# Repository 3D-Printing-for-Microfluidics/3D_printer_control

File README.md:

# 3D Printer Control System

A sophisticated control system for custom DLP-SLA 3D printers, built with Flask and WebSocket communication. This system provides a robust web interface for controlling and monitoring 3D printing operations, with support for various hardware configurations and real-time feedback.

# Overview

This system is designed to control custom DLP-SLA 3D printers using a JSON-based print file format. The print files are validated using a custom JSON schema validator to ensure proper formatting and compatibility. The system supports multiple printer configurations and can be adapted to different hardware setups through its modular architecture.

## System Architecture

### Backend
- Built on Flask web server with modular blueprint structure
- Uses Socket.IO for real-time bidirectional communication between frontend and backend
- Implements a modular hardware driver system for various printer components
- Database-driven job queue management using SQLAlchemy
- Comprehensive logging system with configurable levels and file rotation
- Error handling and recovery mechanisms for hardware failures

### Frontend
- JINJA2 templating engine for HTML structure
- Bootstrap (Darkly theme) for responsive styling
- JavaScript libraries:
  - Socket.IO for real-time communication
  - AJAX for asynchronous requests
  - jQuery for DOM manipulation
  - Popper.js for tooltips and popovers
- Dynamic UI updates for real-time printer status
- Responsive design for various screen sizes

## Hardware Configuration

The system uses a flexible hardware configuration system that:
- Loads hardware configurations based on device hostname
- Supports multiple types of hardware drivers:
  - Virtual hardware (screen, coord_systems, external_control)
  - Abstract base classes and generic drivers (e.g., Visitech light engine, ACS XY/BP stage, Hexapod TTR/focus stage)
  - Regular hardware drivers
- Includes firmware management capabilities through `flash_firmware.sh` RPi script
- Provides dummy drivers for testing and development
- Supports hardware-specific calibration and configuration
- Implements hardware abstraction layers for consistent control interfaces

### Hardware Types
1. **Motion Control**
   - XY stages (ACS, custom implementations)
   - Z-axis control
   - Build plate control
   - Tip-tilt-rotate (TTR) stages
   - Focus stages

2. **Light Control**
   - DLP light engines
   - Screen control systems

3. **Sensors**
   - Load cells
   - Keyence sensors
   - Environmental sensors
   - Accelerometers
   - Light measurement systems

4. **Auxiliary Systems**
   - Vacuum control
   - GPIO control
   - Film control
   - Environmental monitoring

## Core Components

### Manual Controls
- Each hardware driver has associated frontend controls
- Automatically populated based on hardware configuration
- Provides fine-grained control over hardware components
- Allows modification of system settings
- Real-time feedback and status updates
- Safety interlocks and emergency stop functionality

### Views
1. **Print History**
   - Displays recent prints with detailed information
   - Enables job download and re-queue functionality
   - Print success/failure statistics
   - Job parameter history

2. **Server Logs**
   - Shows last 2 weeks of logs
   - Includes calibration position logs
   - Hardware-specific diagnostic information
   - Error tracking and debugging tools

3. **Calibration**
   - Manages printer calibration settings
   - Supports focus, tip, tilt adjustments
   - Integrates with Keyence sensors and Hexapod systems
   - Calibration profile management
   - Automated calibration routines

### Main Printer Control (home.py)
The central control system that:
- Manages print uploads and job queue
- Handles printer planarization
- Controls print operations (start/pause/resume/stop)
- Provides real-time feedback (loadcell data, log messages)
- Implements a dynamic class hierarchy for hardware control
- Error handling and recovery
- State management and synchronization

## Hardware Control Architecture

The system uses a dynamic class composition approach:
- Base `print_control` class defines core functionality
- Hardware-specific subclasses extend functionality
- Class composition is determined by hardware configuration
- Import order is critical for proper initialization and print operations
- Thread-safe operation handling
- Event-driven architecture for hardware interactions

# Raspberry Pi Deployment

This section details the setup process for deploying the system on a Raspberry Pi 5 with NVME storage. See also the `How to do a full install of a HR5 Raspberry Pi` ProjectWiki page for a more detailed guide with rationale.

### Hardware Requirements

- Raspberry Pi 5
- Pimoroni NVME base
- Crucial P3 Plus 1TB SSD (or compatible)
- External SSD housing (for initial setup)

### Initial Setup

1. **Physical Setup**
   - Install NVME SSD and Pimoroni NVME base
   - Follow [Pimoroni NVME base tutorial](https://learn.pimoroni.com/article/getting-started-with-nvme-base)

2. **OS Installation**
   - Download Raspberry Pi Imager
   - Flash Raspberry Pi OS (64-bit) 2024-03-15
   - Configure initial settings:
     - Set hostname (e.g., HR5, MR1v1, HR3v3)
     - Username: pi
     - Password: 3dprinter
     - Timezone: Denver
     - Enable SSH

3. **System Configuration**
   - Configure SSD boot:
     ```bash
     # Edit /boot/firmware/config.txt
     dtparam=pciex1
     nvme_core.default_ps_max_latency_us=0 pcie_aspm=off
     
     # Configure EEPROM
     sudo rpi-eeprom-config --edit
     # Set:
     BOOT_ORDER=0xf416
     PCIE_PROBE=1
     ```
   - Set system clock: `date -s 'YYYY-MM-DD HH:MM:SS'`
   - Configure network:
     - Connect to BYU-Wifi via https://onboard.byu.edu/guest/public/index.html
     - Set static ethernet address (192.168.0.1/24) using `sudo nmtui`
   - Switch to legacy X11:
     ```bash
     sudo raspi-config
     # Advanced Options -> Wayland -> X11
     ```
   - Disable screen blanking:
     ```bash
     sudo raspi-config
     # Display Options -> Screen Blanking -> No
     ```

4. **USB Device Configuration**
   - Create udev rules for USB devices:
     ```bash
     # Wintech
     sudo nano /etc/udev/rules.d/99-wintech.rules
     SUBSYSTEM=="usb",ATTRS{idVendor}=="0451",ATTRS{idProduct}=="c900",GROUP="users",MODE:="0666"
     
     # MKS Controller
     sudo nano /etc/udev/rules.d/99-mks.rules
     SUBSYSTEM=="usb",ATTRS{idVendor}=="0403",ATTRS{idProduct}=="6001",GROUP="users",MODE:="0666"
     
     # Thorlabs Power Meter
     sudo nano /etc/udev/rules.d/99-thorlabspm100.rules
     SUBSYSTEM=="usb",ATTRS{idVendor}=="1313",ATTRS{idProduct}=="8072",GROUP="users",MODE:="0666"
     ```
   - Reload udev rules: `sudo udevadm control --reload-rules`

5. **System Logging**
   - Configure journald:
     ```bash
     # Edit /etc/systemd/journald.conf
     [Journal]
     MaxRetentionSec=1week
     MaxFileSec=1day
     
     # Create journal directory
     mkdir /var/log/journal
     sudo systemd-tmpfiles --create --prefix /var/log/journal
     ```

### Software Installation

1. **Clone Repositories**
   ```bash
   git clone https://github.com/3D-Printing-for-Microfluidics/IP_address_service.git
   git clone https://github.com/gregnordin/3D_printer_control.git
   ```

2. **Install IP Address Service**
   ```bash
   cd IP_address_service/ip_address_service
   sudo -s source ip_address_service_setup.sh
   ```

3. **Setup Python Environment**
   ```bash
   cd 3D_printer_control
   python -m venv env
   source env/bin/activate
   mkdir logs
   
   # Upgrade pip and setuptools
   pip install pip --upgrade
   pip install setuptools --upgrade
   ```

4. **Install Galil Driver**
   ```bash
   # Install CGLib Software
   sudo apt install ./requirements/galil-release_1_all.deb
   sudo apt update
   sudo apt install gclib gcapsd
   ```

5. **Install Python Dependencies**
   ```bash
   pip install -r requirements/prod.txt  # For production
   # or
   pip install -r requirements/dev.txt   # For development
   ```

   Key dependencies include:
   - Flask 3.0.3 with Flask-SocketIO 5.3.6 for web server and real-time communication
   - SQLAlchemy 2.0.31 and Flask-SQLAlchemy 3.1.1 for database management
   - Hardware control libraries:
     - gclib for Galil motion controllers
     - gpiod 2.2.0 and gpiozero 2.0.1 for GPIO control
     - pyserial 3.5 for serial communication
     - pyusb 1.2.1 for USB device control
   - Scientific computing:
     - numpy 2.0.0 and scipy 1.14.1 for numerical operations
     - matplotlib 3.10.1 for plotting
     - pandas 2.2.3 for data manipulation
   - Hardware-specific:
     - ThorlabsPM100 1.2.2 for power meter control
     - seabreeze 2.9.2 for spectrometer integration
     - PIPython 2.10.2.1 for PI motion controllers
   - System utilities:
     - psutil 6.0.0 for system monitoring
     - zeroconf 0.132.2 for network discovery
   - Development tools:
     - jsonschema 4.22.0 for JSON validation
     - scapy 2.5.0 for network analysis

6. **Setup Flask Database**
   ```bash
   source rpi/flask_db_setup.sh
   ```

7. **Configure Systemd Service**
   ```bash
   # Allow X server access
   export DISPLAY=:0.0
   xhost si:localuser:pi
   
   # Create service file
   sudo nano /etc/systemd/system/3d-printer-server.service
   ```
   Add to service file:
   ```ini
   [Unit]
   Description=3D Printer Server
   After=network.target
   
   [Service]
   Type=simple
   WorkingDirectory=/home/pi/3D_printer_control
   Environment=FLASK_APP=/home/pi/3D_printer_control/autoapp.py
   Environment=XAUTHORITY=/home/pi/.Xauthority
   Environment=DISPLAY=:0.0
   ExecStart=/home/pi/3D_printer_control/env/bin/python /home/pi/3D_printer_control/autoapp.py
   Restart=always
   
   [Install]
   WantedBy=multi-user.target
   ```
   Enable and start service:
   ```bash
   sudo systemctl daemon-reload
   sudo systemctl enable 3d-printer-server.service
   sudo systemctl start 3d-printer-server.service
   ```

### Display Configuration

1. **Setup Custom Resolutions**
   ```bash
   # Create autostart directory
   mkdir -p ~/.config/autostart
   
   # Create desktop entry
   nano ~/.config/autostart/xrandr.desktop
   ```
   Add to desktop entry:
   ```ini
   [Desktop Entry]
   Type=Application
   Exec=/home/pi/.config/autostart/xrandr.sh
   Hidden=false
   NoDisplay=false
   X-GNOME-Autostart-enabled=true
   Name[en_US]=Xrandr
   Name=Xrandr
   Comment[en_US]=Set custom resolution using xrandr
   Comment=Set custom resolution using xrandr
   ```
   
   Create resolution script:
   ```bash
   nano ~/.config/autostart/xrandr.sh
   ```
   Add to script:
   ```bash
   #!/bin/sh
   export DISPLAY=:0.0
   
   # Visitech resolution (2560x1600)
   xrandr --newmode "2560x1600_30" 132.68 2560 2608 2640 2720 1600 1603 1609 1623 +hsync -vsync
   xrandr --addmode HDMI-1 2560x1600_30
   xrandr --output HDMI-1 --mode 2560x1600_30
   
   # Wintech resolution (1920x1080)
   xrandr --newmode "1920x1080_60" 148.50 1920 2008 2096 2200 1080 1084 1089 1125 +hsync -vsync
   xrandr --addmode HDMI-2 1920x1080_60
   xrandr --output HDMI-2 --mode 1920x1080_60
   ```
   Make script executable:
   ```bash
   chmod +x ~/.config/autostart/xrandr.sh
   ```

### Additional Hardware Notes

- Spectrometer: Update firmware to NI-VISA version using Thorlabs Driver Switcher
- PI Hexapod stage: Update IP address to match subnet (192.168.x.x)
- ACS stages: Configure static IP and update to match subnet

# Development Setup

### Prerequisites
- Python 3.5 or higher
- Virtual environment (recommended)
- Required Python packages (see requirements/dev.txt)
- Git

### Installation Steps
1. Clone the repository
2. Create and activate virtual environment:
   ```bash
   python -m virtualenv env
   source env/bin/activate  # On Windows: env\Scripts\activate
   ```
3. Install dependencies:
   ```bash
   pip install -r requirements/dev.txt
   ```
4. Set up environment variables:
   ```bash
   export FLASK_APP=tests/dummy_server.py
   export FLASK_DEBUG=1  # For development mode
   ```
5. Initialize database:
   ```bash
   flask db init
   flask db migrate
   flask db upgrade
   ```

### Running the Development Server
1. Start the server:
   ```bash
   python $FLASK_APP
   ```
2. Access the web interface at `http://127.0.0.1:5000`
3. For external access, modify `app.py` to use `0.0.0.0:port`

### Development Tips
- Use Incognito mode to prevent browser caching
- Press `Ctrl+F5` in Chrome to force refresh
- Monitor terminal output for debug information
- Check logs in `printer_server/logs/`

# Active Branches

This repository maintains several branches for different printer configurations:
- `master` - Stable branch for 3D printers
- `dev/ branches` - Current active development branches
- `feature/ branches` - Branches adding new feature to 3D printers
- `stable/ branches` - Legacy release branches no longer in use
- `gen1-1` - Legacy software for HR1.1 3D printer

# Troubleshooting

### Common Issues

1. **Hardware Connection**
   - Check USB connections
   - Verify permissions
   - Test hardware directly
   - Check logs for errors

2. **Firmware Issues**
   - Verify firmware version
   - Check flash process
   - Review error logs
   - Test with dummy firmware

3. **Web Interface**
   - Clear browser cache
   - Check Socket.IO connection
   - Verify JavaScript console
   - Test in incognito mode

# Additional Resources

- [Flask Documentation](http://flask.pocoo.org/docs/1.0/quickstart/)
- [Python Virtual Environment Guide](https://docs.python.org/3/tutorial/venv.html)
- [Socket.IO Documentation](https://socket.io/docs/)
- [Bootstrap Documentation](https://getbootstrap.com/docs/)

# License

This project is licensed under the terms specified in the LICENSE.txt file.

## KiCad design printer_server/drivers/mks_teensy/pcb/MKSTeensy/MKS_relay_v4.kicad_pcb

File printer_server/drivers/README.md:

# 3D Printer Hardware Drivers

This directory contains the hardware drivers for controlling various components of the 3D printer system. The drivers are designed with a modular architecture that supports both real hardware and dummy implementations for testing.

## Driver Architecture

The driver system follows a hierarchical design with:
- Abstract base classes in `generic_drivers/` defining common interfaces
- Concrete implementations for specific hardware
- Dummy implementations for testing and development

### Base Classes

The `generic_drivers/` directory contains abstract base classes for different types of hardware:

1. **Stage Drivers**
   - `BPStageDriver`: Build platform stage control
   - `XYStageDriver`: XY motion stage control
   - `FocusStageDriver`: Focus stage control
   - `TTRStageDriver`: Tip-tilt-rotate stage control

2. **Communication Drivers**
   - `EthernetSerial`: Base class for Ethernet-based serial communication
   - `USBSerial`: Base class USB-based serial communication

## Available Drivers

### Motion Control
- `acs/`: ACS motion controller driver
- `galil/`: Galil motion controller driver
- `hexapod/`: Hexapod stage driver
- `thorlabs_apt`: Thorlabs motor driver for KDC101 and LTS stages
- `tiptilt/`: Custom Tip-tilt stage driver for optical alignment

### Light Control
- `screen/`: Screen control system
- `visitech/`: Visitech light engine driver
- `wintech/`: Wintech DLP controller driver

### Sensors
- `accelerometer/`: Accelerometer driver
- `environmental_sensors/`: Environmental monitoring sensors
- `keyence/`: Keyence confocal displacement sensor driver
- `loadcell/`: Load cell sensor for force measurement
- `photodiode/`: Photodiode sensor driver
- `spectrometer/`: Spectrometer driver

### Auxillary Control
- `external_control/`: External control system interface
- `gpio/`: General Purpose I/O control
- `mks/`: MKS 946 pressure controller driver
- `mks_teensy/`: Teensy-based MKS controller and GPIO interface

### Other
- `coord_systems/`: Coordinate system transformation utilities

## Driver Implementation

Each driver follows a common pattern:
1. Inherits from appropriate base class
2. Implements required interface methods
3. Provides hardware-specific functionality
4. Includes error handling and logging
5. Supports both real and dummy implementations

### Example Usage

```python
from printer_server.drivers.galil import Galil, Galil_dummy

# For real hardware
driver = Galil(config_dict=config, log_level=logging.INFO)

# For testing/development
driver = Galil_dummy(config_dict=config, log_level=logging.INFO)
```

## Adding New Drivers

To add a new driver:

1. Create a new directory in `drivers/`
2. Implement the driver class inheriting from appropriate base class
3. Create a dummy implementation for testing
4. Add driver configuration to hardware configuration JSON
5. Update `hardware_configuration.py` to support the new driver

## Testing

Each driver should have:
- A dummy implementation for testing
- Appropriate Manual Control _snip code

## Configuration

Drivers are configured through JSON files in the `hardware_configuration/` directory. Each driver can specify:
- Connection parameters
- Hardware-specific settings
- Dummy mode for testing
- Logging configuration

## Error Handling

Drivers implement comprehensive error handling:
- Connection failures
- Hardware communication errors
- Invalid commands
- Timeout handling
- Recovery procedures

## Logging

All drivers use the Python logging system with:
- Configurable log levels
- Hardware-specific log messages
- Error tracking
- Performance monitoring

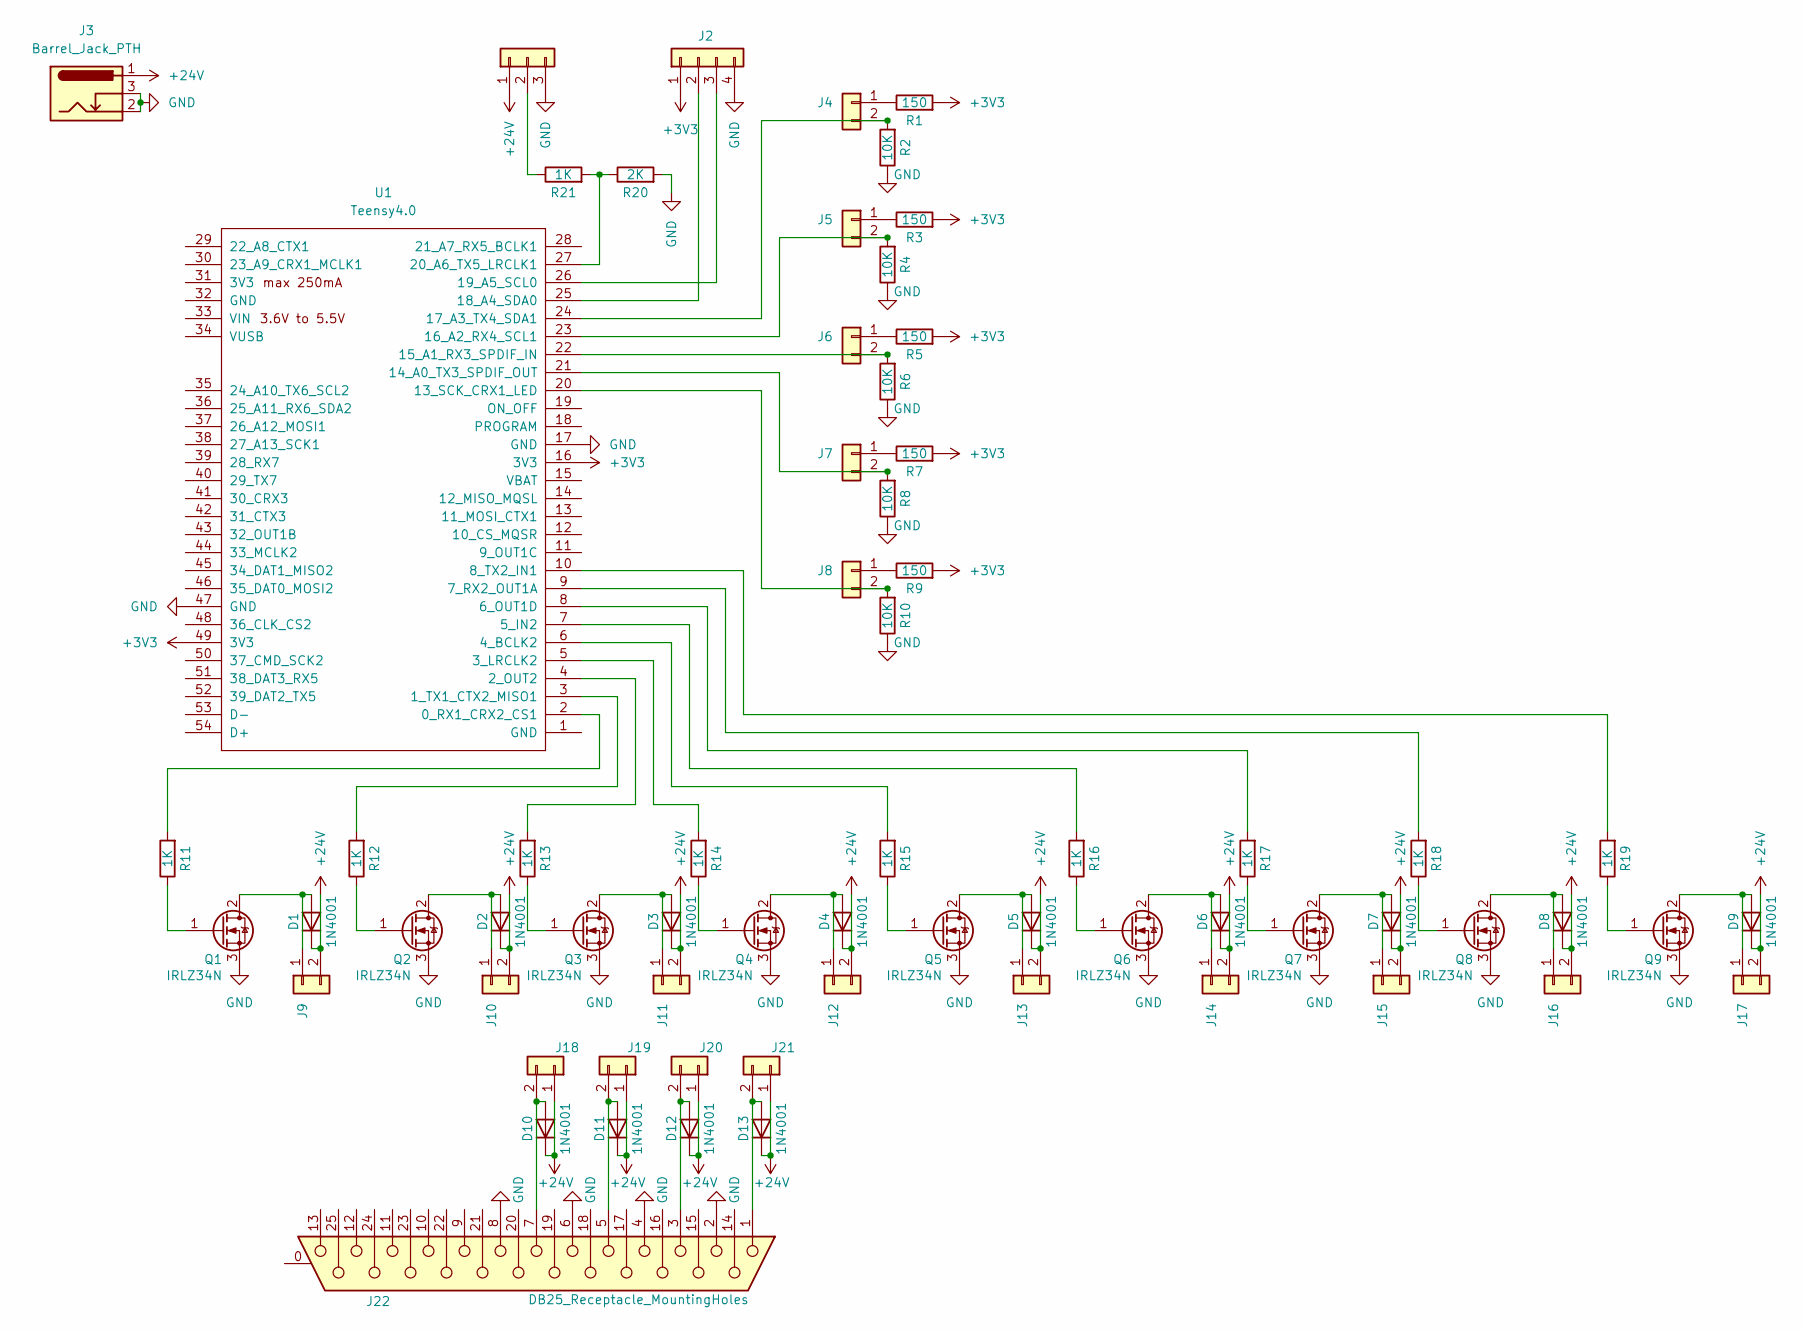
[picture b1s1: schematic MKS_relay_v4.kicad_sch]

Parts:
D1, D2, D3, D4, D5, D6, D7, D8, D9, D10, D11, D12, D13: 1N4001; R_Axial_DIN0204_L3.6mm_D1.6mm_P7.62mm_Horizontal
J1: Conn_01x03; 1x03
J2: Conn_01x04; 1x04
J3: Barrel_Jack_PTH; Power_Jack_PTH
J4, J5, J6, J7, J8, J9, J10, J11, J12, J13, J14, J15, J16, J17, J18, J19, J20, J21: Conn_01x02; 1x02
J22: DB25_Receptacle_MountingHoles; DSUB-25_Female_Horizontal_P2.77x2.84mm_EdgePinOffset4.94mm_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
Q1, Q2, Q3, Q4, Q5, Q6, Q7, Q8, Q9: IRLZ34N; TO-220-3_Vertical
R1, R3, R5, R7, R9: 150; R_Axial_DIN0204_L3.6mm_D1.6mm_P7.62mm_Horizontal
R2, R4, R6, R8, R10: 10K; R_Axial_DIN0204_L3.6mm_D1.6mm_P7.62mm_Horizontal
R11, R12, R13, R14, R15, R16, R17, R18, R19, R21: 1K; R_Axial_DIN0204_L3.6mm_D1.6mm_P7.62mm_Horizontal
R20: 2K; R_Axial_DIN0204_L3.6mm_D1.6mm_P7.62mm_Horizontal
U1: Teensy4.0; Teensy40

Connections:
+3V3: J2.1, R1.2, R3.2, R5.2, R7.2, R9.2, U1.16 (3V3), U1.49 (3V3)
+24V: D1.1 (K), D2.1 (K), D3.1 (K), D4.1 (K), D5.1 (K), D6.1 (K), D7.1 (K), D8.1 (K), D9.1 (K), D10.1 (K), D11.1 (K), D12.1 (K), D13.1 (K), J1.1, J3.1 (PWR), J9.2, J10.2, J11.2, J12.2, J13.2, J14.2, J15.2, J16.2, J17.2, J18.1, J19.1, J20.1, J21.1
GND: J1.3, J2.4, J3.2 (GND), J3.3 (GNDBREAK), J22.2, J22.4, J22.6, J22.8, Q1.3 (S), Q2.3 (S), Q3.3 (S), Q4.3 (S), Q5.3 (S), Q6.3 (S), Q7.3 (S), Q8.3 (S), Q9.3 (S), R2.1, R4.1, R6.1, R8.1, R10.1, R20.2, U1.17 (GND), U1.47 (GND)
unnamed: D1.2 (A), J9.1, Q1.2 (D)
unnamed: D2.2 (A), J10.1, Q2.2 (D)
unnamed: D3.2 (A), J11.1, Q3.2 (D)
unnamed: D4.2 (A), J12.1, Q4.2 (D)
unnamed: D5.2 (A), J13.1, Q5.2 (D)
unnamed: D6.2 (A), J14.1, Q6.2 (D)
unnamed: D7.2 (A), J15.1, Q7.2 (D)
unnamed: D8.2 (A), J16.1, Q8.2 (D)
unnamed: D9.2 (A), J17.1, Q9.2 (D)
unnamed: D10.2 (A), J18.2, J22.7
unnamed: D11.2 (A), J19.2, J22.5
unnamed: D12.2 (A), J20.2, J22.3
unnamed: D13.2 (A), J21.2, J22.1
unnamed: J1.2, R21.1
unnamed: J2.2, U1.25 (18_A4_SDA0)
unnamed: J2.3, U1.26 (19_A5_SCL0)
unnamed: J4.1, R1.1
unnamed: J4.2, R2.2, U1.24 (17_A3_TX4_SDA1)
unnamed: J5.1, R3.1
unnamed: J5.2, R4.2, U1.23 (16_A2_RX4_SCL1)
unnamed: J6.1, R5.1
unnamed: J6.2, R6.2, U1.22 (15_A1_RX3_SPDIF_IN)
unnamed: J7.1, R7.1
unnamed: J7.2, R8.2, U1.21 (14_A0_TX3_SPDIF_OUT)
unnamed: J8.1, R9.1
unnamed: J8.2, R10.2, U1.20 (13_SCK_CRX1_LED)
unnamed: Q1.1 (G), R11.1
unnamed: Q2.1 (G), R12.1
unnamed: Q3.1 (G), R13.1
unnamed: Q4.1 (G), R14.1
unnamed: Q5.1 (G), R15.1
unnamed: Q6.1 (G), R16.1
unnamed: Q7.1 (G), R17.1
unnamed: Q8.1 (G), R18.1
unnamed: Q9.1 (G), R19.1
unnamed: R11.2, U1.2 (0_RX1_CRX2_CS1)
unnamed: R12.2, U1.3 (1_TX1_CTX2_MISO1)
unnamed: R13.2, U1.4 (2_OUT2)
unnamed: R14.2, U1.5 (3_LRCLK2)
unnamed: R15.2, U1.6 (4_BCLK2)
unnamed: R16.2, U1.7 (5_IN2)
unnamed: R17.2, U1.8 (6_OUT1D)
unnamed: R18.2, U1.9 (7_RX2_OUT1A)
unnamed: R19.2, U1.10 (8_TX2_IN1)
unnamed: R20.1, R21.2, U1.27 (20_A6_TX5_LRCLK1)

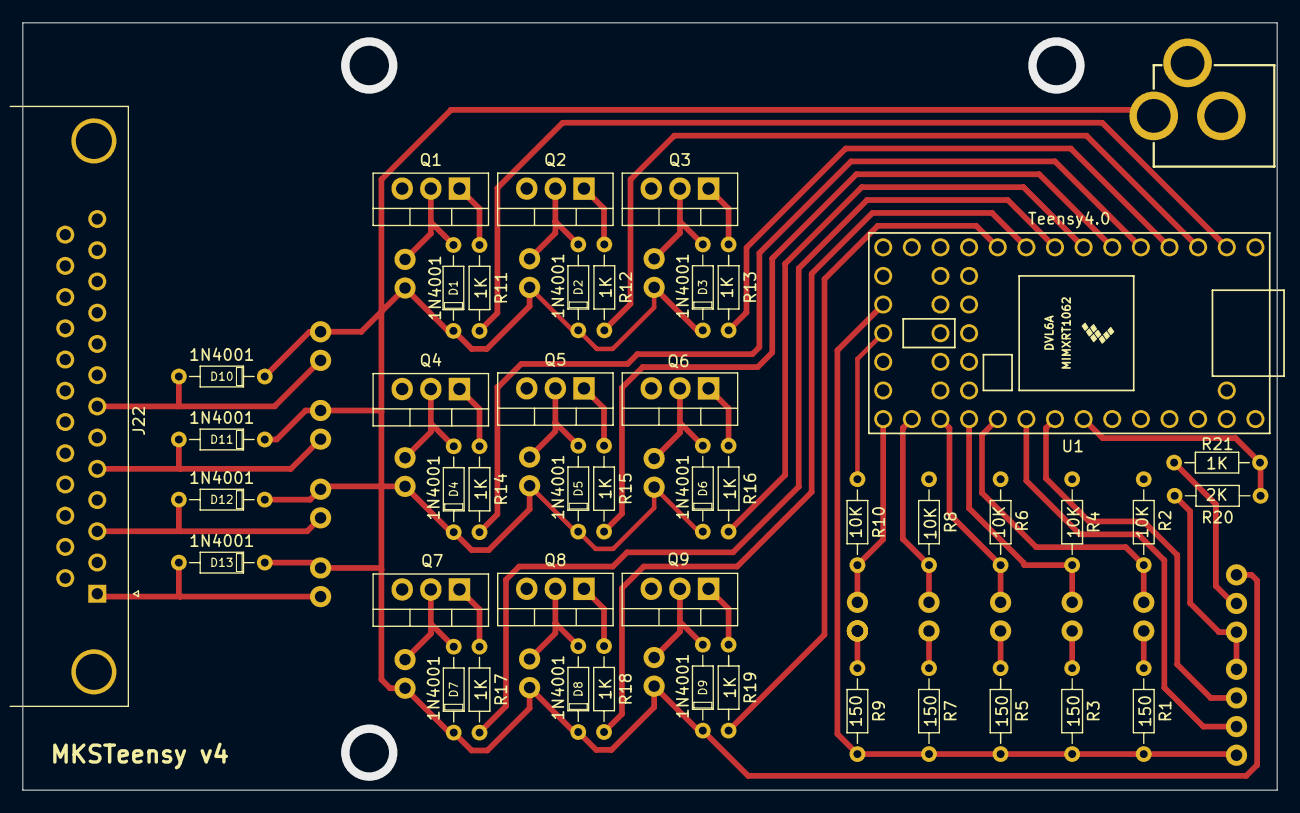
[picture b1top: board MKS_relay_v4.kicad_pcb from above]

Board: 2 copper layers, 111.3 x 68.1 mm, 66 parts (0 on the bottom side), 48 nets.

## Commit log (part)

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2024-12-31 Prevent loop racing in TT
2024-12-31 Actually call TTR logging start/stop
2024-12-31 Fix other race events
2024-12-31 speed up keyence measurements
2024-12-31 Remove extra wait in light engine driver exposures
2024-12-31 Increase resolution and update rate of loadcell plot
2024-12-31 Fix bug in GPIO film mc
2024-12-31 Rename tt log
2025-01-02 Fixed Tiptilt driver float rounding
2025-01-02 Change last commit to increse precision
2025-01-02 One more...
2025-01-02 Fix cast error in KDC
2025-01-03 Fix ttr bug in calibration
2025-01-03 Fix trig error in MirrorTipTilt
2025-01-03 Add undef if tt not initialized. Speed up movements
2025-01-03 Add nm label to le source
2025-01-09 Add microcode libraries, firmware scripts, and firmware binaries
2025-01-09 Split mks and mks_teensy, also a few bug fixes
2025-01-09 Fix bug introduced in f4f2584
2025-01-31 Reduce loadcell drawing
2025-01-31 Hopefully fix TT loop failing
2025-01-31 Reduce loadcell planarization to 35N
2025-01-31 Update HR5 settings (note grayscale corr is included...)
2025-01-31 Add grayscale corrections
2025-01-31 Add TestControl
2025-01-31 Update light_measurement_control
2025-01-31 Add second finish plan for HR5
2025-02-24 Add more delay to degas vent
2025-02-24 First pass at test code for hannah and heidi
2025-02-24 Fix bug in last
2025-02-24 Add multiple scan lines to test
2025-03-07 Add vaccum control for prints (still need to do some kind of json enabling)
2025-03-07 Add logging to last commit
2025-03-07 Adjusting vacuum targets
2025-03-07 Add extra check ot bell jar venting
2025-03-07 Move MKSControl before LoadcellControl
2025-03-07 Fix critical bug
2025-03-07 Fix bug in vaccum control
2025-03-10 Add "Print under vacuum" to json and add planarization vacuum logging
2025-03-10 Cleanup loadcell set_log_file
2025-03-10 Only do planarization a 2nd time if "Print under vacuum"
2025-03-10 Fix bug in new vaccum code
2025-03-10 Another fix to vacuum code
2025-03-13 Add Y-offset to keyence line test
2025-03-17 Hopefully fix accelerometer freezing
2025-03-19 Fix issue with vacuum valve priorities
2025-03-21 Still trying to fix hanging at end of print
2025-03-25 Worked on grayscale scan and analysis test code
2025-03-25 Speed up print and add correction
2025-03-25 Fix bug in last commit
2025-03-28 Change fast photodiode position
2025-03-28 Tweek last commit
2025-04-09 Add film membrane to json and validator
2025-04-09 Recompress cleaned uploaded file
2025-04-11 Update requirements again
2025-04-11 Updated installation README and files to save galil/gclib install files
2025-04-11 Updated reqirements to include gclib
2025-04-14 Add normaization factor of 1 to 3v3u json
2025-04-14 Fix bug in normalization base case
2025-04-15 Fix bug in MR1v1 calibration
2025-04-19 Add thermal drift calculations for MR1v1
2025-04-19 Fix bugs in new keyence thermal code
2025-04-19 Fix bug in grayscale on visitech
2025-04-19 Fix another bug in the thermal code
2025-04-19 Tweek progress bar
2025-04-19 Add debug statements to new keyence measurements
2025-04-19 Trying to figure out what is not working
2025-04-20 Switch temporary print statements to event log
2025-04-21 Clean up code, add origin thermal measure, and fix crash
2025-04-21 Correct for backlash in griffin focus & add thermal expantion log
2025-04-21 Fix bug in thermal logging
2025-04-21 Another bug
2025-04-21 Remove keyence focus stage jiggle
2025-04-21 Final cleanup
2025-04-22 Remove temp logging, move all keyence logs to log file, swap origin measurement to only failed cont measurements
2025-04-22 Fix bug
2025-04-22 Update again
2025-04-22 Again
2025-04-23 Fix typo
2025-05-09 Add wintech fan control
2025-05-09 More bug fix
2025-05-09 Set fans to be default on
2025-05-09 Swap fan polarity
2025-05-09 Undo last
2025-05-09 Final fan commit
2025-07-28 Fix bug in dev.txt
2025-07-28 Update 3v3u loadcell settings
2025-07-29 update to galil controller
2025-07-30 Update KDC and os1 hardware config
2025-07-30 Fixed os1v0 hw-conf and renamed kdc101
2025-07-30 Fix os1 loadcell pid
2025-07-30 Fix hw-conf
2025-07-30 Fix multi-inheritance of thorlabs-apt driver
2025-07-31 Fix apt limits bug
2025-07-31 Add delay after apt home
2025-07-31 Update ttrf limits to use rad
2025-07-31 Update os1 coords, speeds, limits, and homing speeds
2025-07-31 Update 3 series to use kdc101_ttrf
2025-08-01 Fix apt connect
2025-08-01 Fix apt limit issues
2025-08-01 Update apt homing speeds
2025-08-01 Tweek log messages
2025-08-01 Cleanup apt
2025-08-01 Fix limits
2025-08-01 Fix bug in ttrf limits
2025-08-01 Update bp, xy, focus limits to update on mc
2025-08-01 Double tip/tilt angles
2025-08-05 updated serial number
2025-08-05 planarization motor initialization bugfixes
2025-08-05 planarization motor initialization bug fixes
2025-08-05 bug fixes
2025-08-05 updated planarization firmware
2025-08-05 firmware flashing bug fixed?
2025-08-05 turned on dummy drivers for testing
2025-08-05 firmware flashing name reconcilliation
2025-08-06 small bug squash
2025-08-06 Update OS1 hwconf
2025-08-06 Fix bugs in motor planarization
2025-08-06 fixed pointer issue
2025-08-06 Fix bug in planarization threading
2025-08-07 Mostly finish motorized planarization
2025-08-07 added supported versions
2025-08-07 Fix bug in ttr join
2025-08-07 Fix bug in clickable row
2025-08-08 Add first pass at keyence tip/tilt
2025-08-12 separation of photodiode and spectrometer in light measurement control
2025-08-12 Add in Visitech initialization check
2025-08-12 manual controls for planarization motor
2025-08-12 intuitive change so that loosen sets target torque to 0.0
2025-09-05 Add orientation to config json
2025-09-05 Update OS1 coords
2025-09-05 Adjust OS1 speeds and accelerations
2025-09-05 Adjust OS1 planarization settings
2025-09-05 Try to fix rare screen drawing failure
2025-09-05 Tweek kdc101ttrf tip multiplier
2025-09-05 Adjust visitech DMD operation to wait until video lock
2025-09-05 Force visitech to validate video lock on init
2025-09-05 Add 999 schema to OS1
2025-09-05 Swap auto_tip_tilt to test control
2025-09-05 Overhaul test control (progress, le alignment, stage linking, new photodiode centering process, grayscale json updating, keyence/photodiode tip/tilt) BROKEN HR5 MIRRORING
2025-09-05 Fix bugs in and tweek planarization
2025-09-18 Fix bug in MR1 Visitech focus
2025-10-15 Add variables to print schema
2025-10-15 Add simpleeval req
2025-10-15 Fix last
2025-10-16 Update HR5 coords, vacuum levels, and grayscale correction code
2025-10-16 Add logging to screen image not found
2025-10-16 Add calibration images to visitech
2025-10-16 Remove print statement
2025-10-16 Add grayscale correction image to OS1 hwconf
2025-10-16 Rename keyence control
2025-10-16 Update test_control plotting and use builtin calibration images
2025-10-16 Update gitignore
2025-11-19 Update MR1v1 coords
2025-11-19 Update json validator with membrane on film change
2026-01-29 debugging on printer pi
2026-02-09 Updated to json v5
2026-02-09 Fix schema bug
2026-02-09 Take 2
2026-02-09 Take 3
2026-02-09 Ok. For reals this time??
2026-02-10 Fix bug in squeeze force and add debug print for testing
2026-02-10 Remove debug prints
2026-02-10 Fixed last
2026-02-10 Fix printer_compatibiliy vaccum check
2026-02-10 Add wait time to "print on film" technique
2026-02-10 Increase max print history length from 500 to 2500
2026-02-16 Fix some broken code on OS1 branch
2026-02-16 Update 3 series ttrf to match os1
2026-02-16 Implement calibration prints
2026-02-16 Removed info and fixed variables to be pythonic
2026-02-16 Try alternate rendering for prints
2026-02-16 Adjusted print file names and layout. (also renamed calibration print)
2026-02-17 Add debug prints
2026-02-17 Fix translation dict
2026-02-17 First test of active irradiance correction
2026-02-17 Add debug print
2026-02-17 Fixed bugs
2026-02-17 Rearranged calibration parameters
2026-02-17 Try to get group headers
2026-02-17 Tweek irradinace names
2026-02-17 Try to fix broken buttons
2026-02-18 Add sweep and uniform focus prints
2026-02-18 Limit calibration prints and add header
2026-02-18 Adjust print file name display
2026-02-18 Increase header size
2026-02-18 Fix bug in new active irradance correction
2026-02-18 Update OS1 hw config
2026-02-19 Fix bug with visitechs not init-ing
2026-02-20 Update calibration print files
2026-02-20 Added timeout to loadcell planarization
2026-02-20 Fix bug in defocus
2026-02-20 Change permissions of reset HDMI
2026-03-04 A few tweeks to focus stage linking
2026-03-04 Add Tip/Tilt focus print
2026-03-04 Add calibration prints to os1
2026-03-04 Update tt focus cal print readme
2026-03-04 Update print again
2026-03-04 Update cal readmes and add grayscale correction cal
2026-03-04 Add grayscale cal print to os1
2026-03-09 Update HR5 grayscale calibration
2026-03-23 Changed calibration prints to load from zip
2026-03-23 Remove non-zipped calibration prints
2026-03-23 Fix bug in galil stage homing
2026-03-23 Fix bug in loadcell planarization
2026-03-23 Update calibration print
2026-03-25 Added search, filter, and sort to print history
2026-03-31 Fix issues in backfill script
2026-03-31 Update calibration prints
2026-03-31 Add image mirroring to JSON
2026-03-31 Add image mirroring to hwconfig
2026-03-31 Add design header to v999 schema
2026-03-31 Fix print history column selector layout
2026-03-31 Fixed bugs in stage limits (couldn't disable)
2026-03-31 Moved auto_focus parameters to respective hardware
2026-03-31 Add parameter for keyence direct_focal_measurement and thermal_drift_measurement
2026-03-31 Reorganized calibration page
2026-03-31 Cleanup test_control and fix some broken tests
2026-03-31 Standarize motion command on threaded movement
2026-03-31 Round all motion stages to 4 digits of precision
2026-03-31 Fix bugs in 3 series hwconfig
2026-03-31 Get grayscale correction mapping working with new mirroring
2026-03-31 Fix image stitching
2026-03-31 Cleanup code
2026-04-09 Add prev_position setter in jogging
2026-04-09 Remove bp from coordinate system
2026-04-09 Fix bug in extract calibration order
2026-04-09 Move all moves to threaded functions, add xyf move function, and fix keyence focus
2026-04-09 Add OS1 stitching alignment print
2026-04-09 Remove old code
2026-04-09 Fix bug in test control (center tt)
2026-04-14 Update HDMI reset to also reset tkinter virtual screen
2026-04-14 tweek backfill script
2026-05-07 Fix code bug in focus stage linking
2026-05-11 Fix rare bugs where print fails to start
2026-05-14 Suppress wintech warning on MR1 print finish
2026-05-19 Add audio cues
2026-05-19 Update dummy drivers
2026-05-19 Fix bugs in mc loadcell start
2026-05-22 HR3v3u grayscale correction
2026-05-22 Adjust print sounds
2026-05-26 Update HR3v3u TTRF
2026-05-26 Update HR3v3u normalization
2026-05-26 Add HR3v3 and OS1 grayscale/normalization
2026-05-26 Default to normalized
2026-05-26 Update HR3v3 normalization
2026-05-27 Fix bug in grayscale default
2026-05-27 Update 3 series again
2026-05-29 Change sounds
2026-06-01 Update HR3v3 TTRF to new system
2026-06-01 Update auto planarization firmware
2026-06-01 Add auto planarization to HR3v3u
2026-06-04 Change um to μm on mc pages
2026-06-04 Add new grayscale report
2026-06-04 Fix threading bug in xy/focus control
2026-06-05 Update License
2026-06-11 Remove photodiode focus and tip/tilt
2026-06-11 Rename le name conversion function
2026-06-11 Move virtual screen into light engine drivers (missing test_control)
2026-06-11 Update test_control (new screen, grayscale scan transforms, grayscale check only flag, bug fixes in report)
2026-06-11 Fix bug in thorlabs apt mirroring
2026-06-11 Update json readme
2026-06-11 Fix bugs in grayscale default and screen restart
2026-06-11 Update saves prints from 2.5k to 15k
2026-06-12 Fix bug in new grayscale defaults
2026-06-15 Add new models and forms
2026-06-15 Remove unused logging handler
2026-06-17 Add new reqs
2026-06-17 Fix JS bug on home
2026-06-17 Move calibration positions to db & change models to have classmethods
2026-06-17 Fully working sessions
2026-06-23 Lots of work getting tables working
2026-06-23 Fix spelling error
2026-06-29 Add session summary
2026-06-29 Leave all calibrations per session
2026-06-29 Don't log focus_base
